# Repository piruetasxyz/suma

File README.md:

# suma

## About

suma is an open source hardware Eurorack mixer module by [piruetas](https://piruetas.xyz), part of popusintes. It sums three inputs, each with its own potentiometer, into one output, using a TL072 dual op amp (rev-a also had an inverted output, removed in rev-b). The board is made in KiCad 10 with its own local symbol, footprint and 3D model libraries, included in each revision's `bibliotecas/` folder, and the panel is made in OpenSCAD with the shared modules from [popusintes-cajas-paneles](https://github.com/piruetasxyz/popusintes-cajas-paneles), included as a git submodule in `terceros/`. Hardware is licensed under CERN-OHL-P-2.0, and the panel and documentation under CC-BY-SA-4.0 (see [LICENSE.md](./LICENSE.md)). Documentation, schematic, board render and bill of materials (in Spanish): <https://piruetas.xyz/suma/>.

## Acerca de

Mezclador eurorack de [piruetas](https://piruetas.xyz), parte de popusintes, hecho en KiCad y publicado como hardware de código abierto.

Documentación, esquemático, placa y Bill of materials: <https://piruetas.xyz/suma/>.

## Características

- 3 entradas (jacks de 3.5 mm), cada una con su potenciómetro.
- 1 salida: la suma de las entradas (rev-a tenía además una salida con la suma invertida, que rev-b ya no lleva).
- Amplificador operacional dual TL072.
- Alimentación por header Eurorack de 10 pines (2x05), ±12V, con diodos Schottky de protección contra polaridad inversa.
- Placa de 25 × 100 mm, 2 capas.

## Revisiones

- `v0.1 rev-a`: diseñada y fabricada en octubre 2026. No funciona tal como viene armada (ver errores abajo).
- `v0.1 rev-b`: en desarrollo. Corrige las huellas de los diodos y de los potenciómetros, quita la salida invertida (J6 y R8), tiene la placa ruteada de nuevo y agrega el panel.

### Errores conocidos de rev-a

El esquemático está bien; los errores están en las huellas.

- **Diodos D1 y D2 montados al revés.** El símbolo tiene el cátodo (K) en el pin 1, pero la serigrafía de la huella `SOD-123FL_L2.8-W1.8-LS3.7-R-RD` marca el cátodo en el pad 2, y JLCPCB los montó siguiendo la serigrafía. Los diodos quedan en inverso, el TL072 solo recibe la corriente de fuga de los Schottky y los rieles caen a unos ±1.5 V en vez de ±11.7 V. Resultado: la salida sale muy baja (~1 Vpp en vez de 5 Vpp) y deformada.
- **Potenciómetros al revés.** La huella `POT_TH_Alps_RK09K_Single_Vertical` tiene los pads 1 y 3 intercambiados respecto a la huella estándar de KiCad. Girando en sentido horario el cursor va hacia GND (silencio), y en antihorario hacia la entrada (volumen máximo).

Para comprobarlo en una placa: con el módulo alimentado, medir el pin 8 y el pin 4 de U1 (o C1 y C2) respecto a GND. Si da ~±1-2 V en vez de ~±11.7 V, los diodos están al revés.

Arreglo de las placas rev-a ya armadas:

- Desoldar D1 y D2 y soldarlos girados 180°. Para probar rápido, también se pueden puentear con un cable (se pierde la protección contra polaridad inversa).
- Los potenciómetros no tienen arreglo limpio: esas placas funcionan al revés (antihorario = más volumen).

### Simulación

rev-a y rev-b se pueden simular en KiCad (Inspeccionar → Simulador → Ejecutar). Los modelos están en `bibliotecas/spice/`: el TL072 (macro-modelo aproximado; para más precisión reemplazar por el modelo oficial de TI), el 1N5817, y modelos de los conectores para no agregar fuentes al esquemático. J4 se comporta como una fuente de ±12 V, J1-J3 como osciladores senoidales (J1: 5 Vpp a 220 Hz; J2 y J3 en 0 V; se cambian con `amplitud` y `frecuencia` en Sim.Params) y las salidas (J5 y J6 en rev-a, solo J5 en rev-b) como la entrada de 100k de otro módulo. La posición de cada potenciómetro se cambia con `pos` en Sim.Params (1 = horario completo, según el esquemático).

La simulación muestra el circuito tal como está en el esquemático (que funciona: 4.95 Vpp con el potenciómetro al máximo). Para reproducir cómo quedó armada rev-a, cambiar Sim.Pins de D1 y D2 a `1=A 2=K` e invertir `pos` en los potenciómetros.

El PCB de rev-a no se actualizó con los campos de simulación, para que siga siendo igual a lo fabricado. Por eso el DRC con paridad de esquemático muestra 12 avisos de campos `Sim.*` faltantes, que no afectan al circuito.

### Pendientes para rev-b

Ya está hecho en [hardware/suma-v-0-rev-b](./hardware/suma-v-0-rev-b):

- Biblioteca propia `popusintes` ([bibliotecas/popusintes.pretty](./hardware/suma-v-0-rev-b/bibliotecas/popusintes.pretty) y [bibliotecas/popusintes.3dshapes](./hardware/suma-v-0-rev-b/bibliotecas/popusintes.3dshapes)), autocontenida con sus modelos 3D, con dos huellas corregidas:
  - `Diodo_SOD-123FL`: misma geometría y serigrafía que la huella de EasyEDA, con los pads 1 y 2 intercambiados para que el pad 1 (cátodo, K) quede del lado de la barra. Así la serigrafía, los números de pad y la huella de JLCPCB coinciden, y la rotación en el CPL sigue en 0.
  - `Potenciometro_Alpha_RD901F_Vertical`: misma geometría que la huella BYOM (que calza bien con los potenciómetros), con los pads 1 y 3 intercambiados: visto de frente con las patas hacia abajo, pad 1 = pata izquierda (antihorario), pad 3 = pata derecha (horario).
- Sin salida invertida: se quitaron J6 y R8.
- Placa ruteada de nuevo: DRC sin errores, sin conexiones pendientes y sin diferencias con el esquemático.
- Todo renombrado de rev-a a rev-b, incluida la carpeta de salida de los gerbers (`../suma-v-0-rev-b-fab/`), para no pisar los archivos de rev-a.
- Panel en [panel/suma-v-0-rev-b](./panel/suma-v-0-rev-b), con los agujeros de los potenciómetros y jacks en las mismas posiciones que la placa.

Falta:

- [ ] Opcional: acercar C2 al pin 4 de U1 (−12 V); hoy está a unos 10 mm.
- [ ] Simular rev-b en KiCad antes de mandarla a fabricar.
- [ ] Revisar el texto de la serigrafía en un computador con las fuentes del proyecto instaladas antes de generar los gerbers.
- [ ] Generar gerbers, BOM y CPL de rev-b (`hardware/suma-v-0-rev-b-fab` y `hardware/suma-v-0-rev-b-pcba`).
- [ ] En el pedido de JLCPCB, revisar en la vista previa de montaje que la banda de D1 y D2 quede en el pad 1, el izquierdo, del lado de la barra de la serigrafía.
- [ ] Antes de imprimir el panel, confirmar que queda bien de izquierda a derecha visto de frente (potenciómetros a la izquierda, jacks a la derecha), por ejemplo con un panel ya impreso de relo, que usa la misma convención. Después exportar el `.stl`.
- [ ] Actualizar [kicad-retrata.yml](./kicad-retrata.yml) y [docs](./docs) para que apunten a rev-b.
- [ ] Revisar otros módulos de popusintes que usen las mismas huellas de EasyEDA y BYOM: atenu rev-a usa la huella BYOM del potenciómetro con el mismo cableado que suma, así que tiene el mismo error.

## Estructura del repositorio

- [hardware/suma-v-0-rev-a](./hardware/suma-v-0-rev-a): proyecto de KiCad (esquemático y placa), los archivos fuente del diseño.
- [hardware/suma-v-0-rev-a/bibliotecas](./hardware/suma-v-0-rev-a/bibliotecas): símbolos, huellas y modelos 3D usados por el proyecto. Van en el repositorio para que el proyecto de KiCad se abra sin instalar bibliotecas adicionales.
- [hardware/suma-v-0-rev-a-fab](./hardware/suma-v-0-rev-a-fab): gerbers y archivos de taladrado para fabricar la placa.
- [hardware/suma-v-0-rev-a-pcba](./hardware/suma-v-0-rev-a-pcba): lista de componentes y archivo de posiciones para armado en JLCPCB.
- [hardware/suma-v-0-rev-b](./hardware/suma-v-0-rev-b): proyecto de KiCad de rev-b (en desarrollo). Sus [bibliotecas](./hardware/suma-v-0-rev-b/bibliotecas) incluyen la biblioteca propia `popusintes` con las huellas corregidas del diodo y del potenciómetro, y los modelos SPICE en `spice/`.
- [panel/suma-v-0-rev-b](./panel/suma-v-0-rev-b): archivos fuente de OpenSCAD del panel, con los agujeros de los potenciómetros y jacks de la placa rev-b. Se abre [suma.scad](./panel/suma-v-0-rev-b/suma.scad); la versión grabada en el panel está en [versiones.scad](./panel/suma-v-0-rev-b/versiones.scad).
- [terceros/popusintes-cajas-paneles](https://github.com/piruetasxyz/popusintes-cajas-paneles): submódulo de git con las constantes eurorack y las funciones y módulos de OpenSCAD compartidos entre las cajas y paneles de popusintes. Para clonar el repositorio con el submódulo: `git clone --recursive https://github.com/piruetasxyz/suma.git`, o `git submodule update --init` si ya estaba clonado.
- [docs](./docs): documentación, publicada en <https://piruetas.xyz/suma/>. Las capturas del esquemático y de la placa, y la tabla de Bill of materials, las genera [kicad-retrata](https://github.com/piruetasxyz/kicad-retrata) en cada push (ver [kicad-retrata.yml](./kicad-retrata.yml)).
- [LICENSES](./LICENSES): textos completos de las licencias.

## Fabricación

Como es hardware de código abierto, los archivos fuente de KiCad, los archivos de fabricación de [hardware/suma-v-0-rev-a-fab](./hardware/suma-v-0-rev-a-fab), los de armado de [hardware/suma-v-0-rev-a-pcba](./hardware/suma-v-0-rev-a-pcba) y la [Bill of materials](https://piruetas.xyz/suma/#bill-of-materials-v01-rev-a) están publicados para que cualquiera pueda estudiar, modificar y fabricar el diseño. piruetas no da soporte para unidades fabricadas o armadas por terceros.

## Créditos

- Aarón Montoya-Moraga: investigación, esquemático, PCB, fabricación y documentación.

## Licencia

suma es (c) 2026 piruetas SpA / Aarón Montoya-Moraga.

- Hardware (`hardware/`): [CERN-OHL-P-2.0](./LICENSES/CERN-OHL-P-2.0.txt).
- Panel (`panel/`): [CC-BY-SA-4.0](./LICENSES/CC-BY-SA-4.0.txt).
- Documentación (`docs/`): [CC-BY-SA-4.0](./LICENSES/CC-BY-SA-4.0.txt).
- Biblioteca compartida (`terceros/popusintes-cajas-paneles`): submódulo con su propia licencia, MIT.
- El nombre, logo y marca de piruetas no están cubiertos por estas licencias: ver [LicenseRef-piruetas-branding](./LICENSES/LicenseRef-piruetas-branding.txt).

Ver [LICENSE.md](./LICENSE.md) para los detalles. El repositorio sigue la especificación [REUSE](https://reuse.software/).

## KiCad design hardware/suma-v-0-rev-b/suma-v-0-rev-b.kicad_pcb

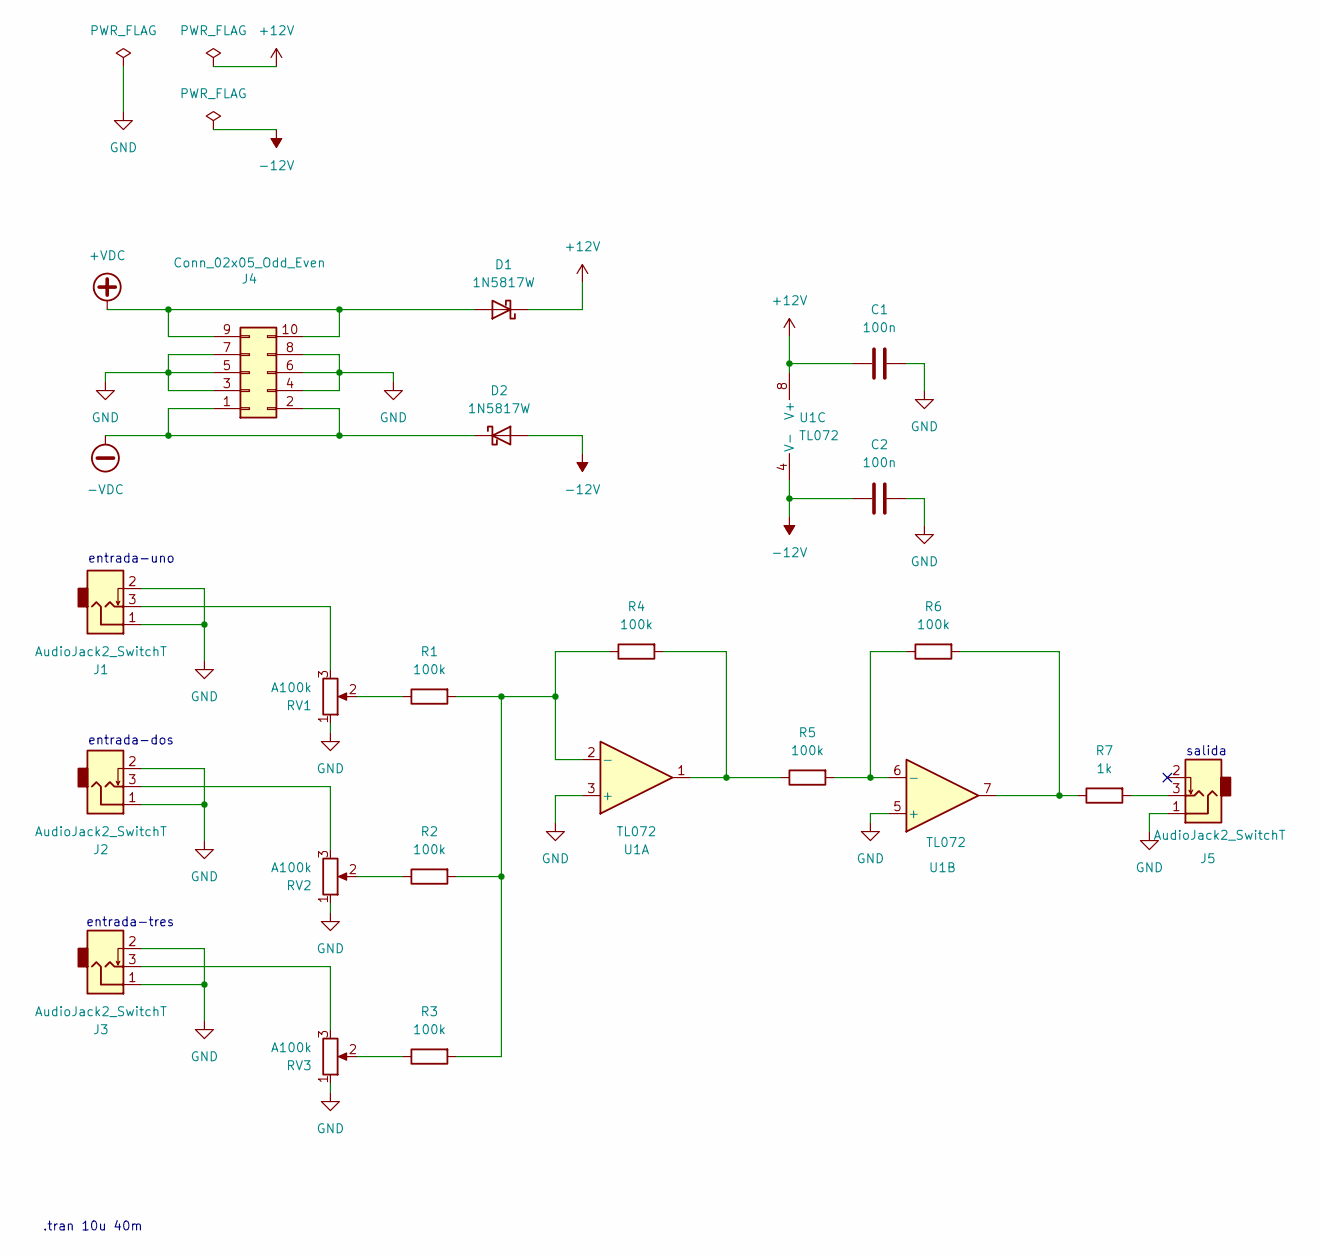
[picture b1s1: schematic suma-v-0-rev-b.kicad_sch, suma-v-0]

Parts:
C1, C2: 100n; C0805; LCSC C49678
D1, D2: 1N5817W; Diodo_SOD-123FL; LCSC C169541
J1, J2, J3, J5: AudioJack2_SwitchT; Jack_3.5mm_QingPu_WQP-PJ398SM_Vertical
J4: Conn_02x05_Odd_Even; IDC-Header_2x05_P2.54mm_Vertical
R1, R2, R3, R4, R5, R6: 100k; R0805; LCSC C25611
R7: 1k; R0805; LCSC C2907232
RV1, RV2, RV3: A100k; Potenciometro_Alpha_RD901F_Vertical
U1: TL072; SOIC-8_L4.9-W3.9-P1.27-LS6.0-BL; LCSC C6962

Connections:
+12V: C1.2, D1.1 (K), U1.8 (V+)
+VDC: D1.2 (A), J4.9, J4.10
-12V: C2.2, D2.2 (A), U1.4 (V-)
-VDC: D2.1 (K), J4.1, J4.2
GND: C1.1, C2.1, J1.1, J1.2, J2.1, J2.2, J3.1, J3.2, J4.3, J4.4, J4.5, J4.6, J4.7, J4.8, J5.1, RV1.1, RV2.1, RV3.1, U1.3 (+), U1.5 (+)
unnamed: J1.3, RV1.3
unnamed: J2.3, RV2.3
unnamed: J3.3, RV3.3
unnamed: J5.3, R7.2
unnamed: R1.1, RV1.2
unnamed: R2.1, RV2.2
unnamed: R3.1, RV3.2
unnamed: R4.2, R5.1, U1.1
unnamed: R6.2, R7.1, U1.7
unnamed: R1.2, R2.2, R3.2, R4.1, U1.2 (-)
unnamed: R5.2, R6.1, U1.6 (-)

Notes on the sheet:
entrada-tres
entrada-uno
salida
.tran 10u 40m
entrada-dos

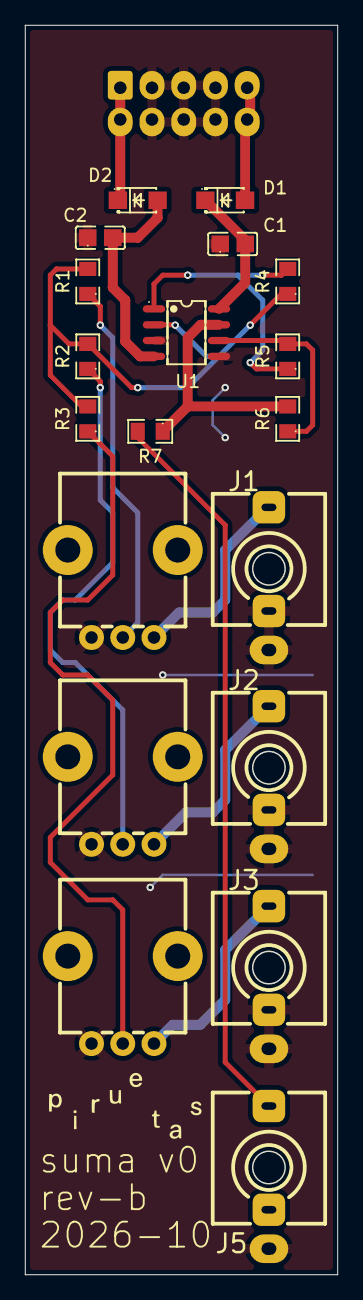
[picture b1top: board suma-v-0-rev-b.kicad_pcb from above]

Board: 2 copper layers, 25.0 x 100.0 mm, 20 parts (1 on the bottom side), 16 nets.
